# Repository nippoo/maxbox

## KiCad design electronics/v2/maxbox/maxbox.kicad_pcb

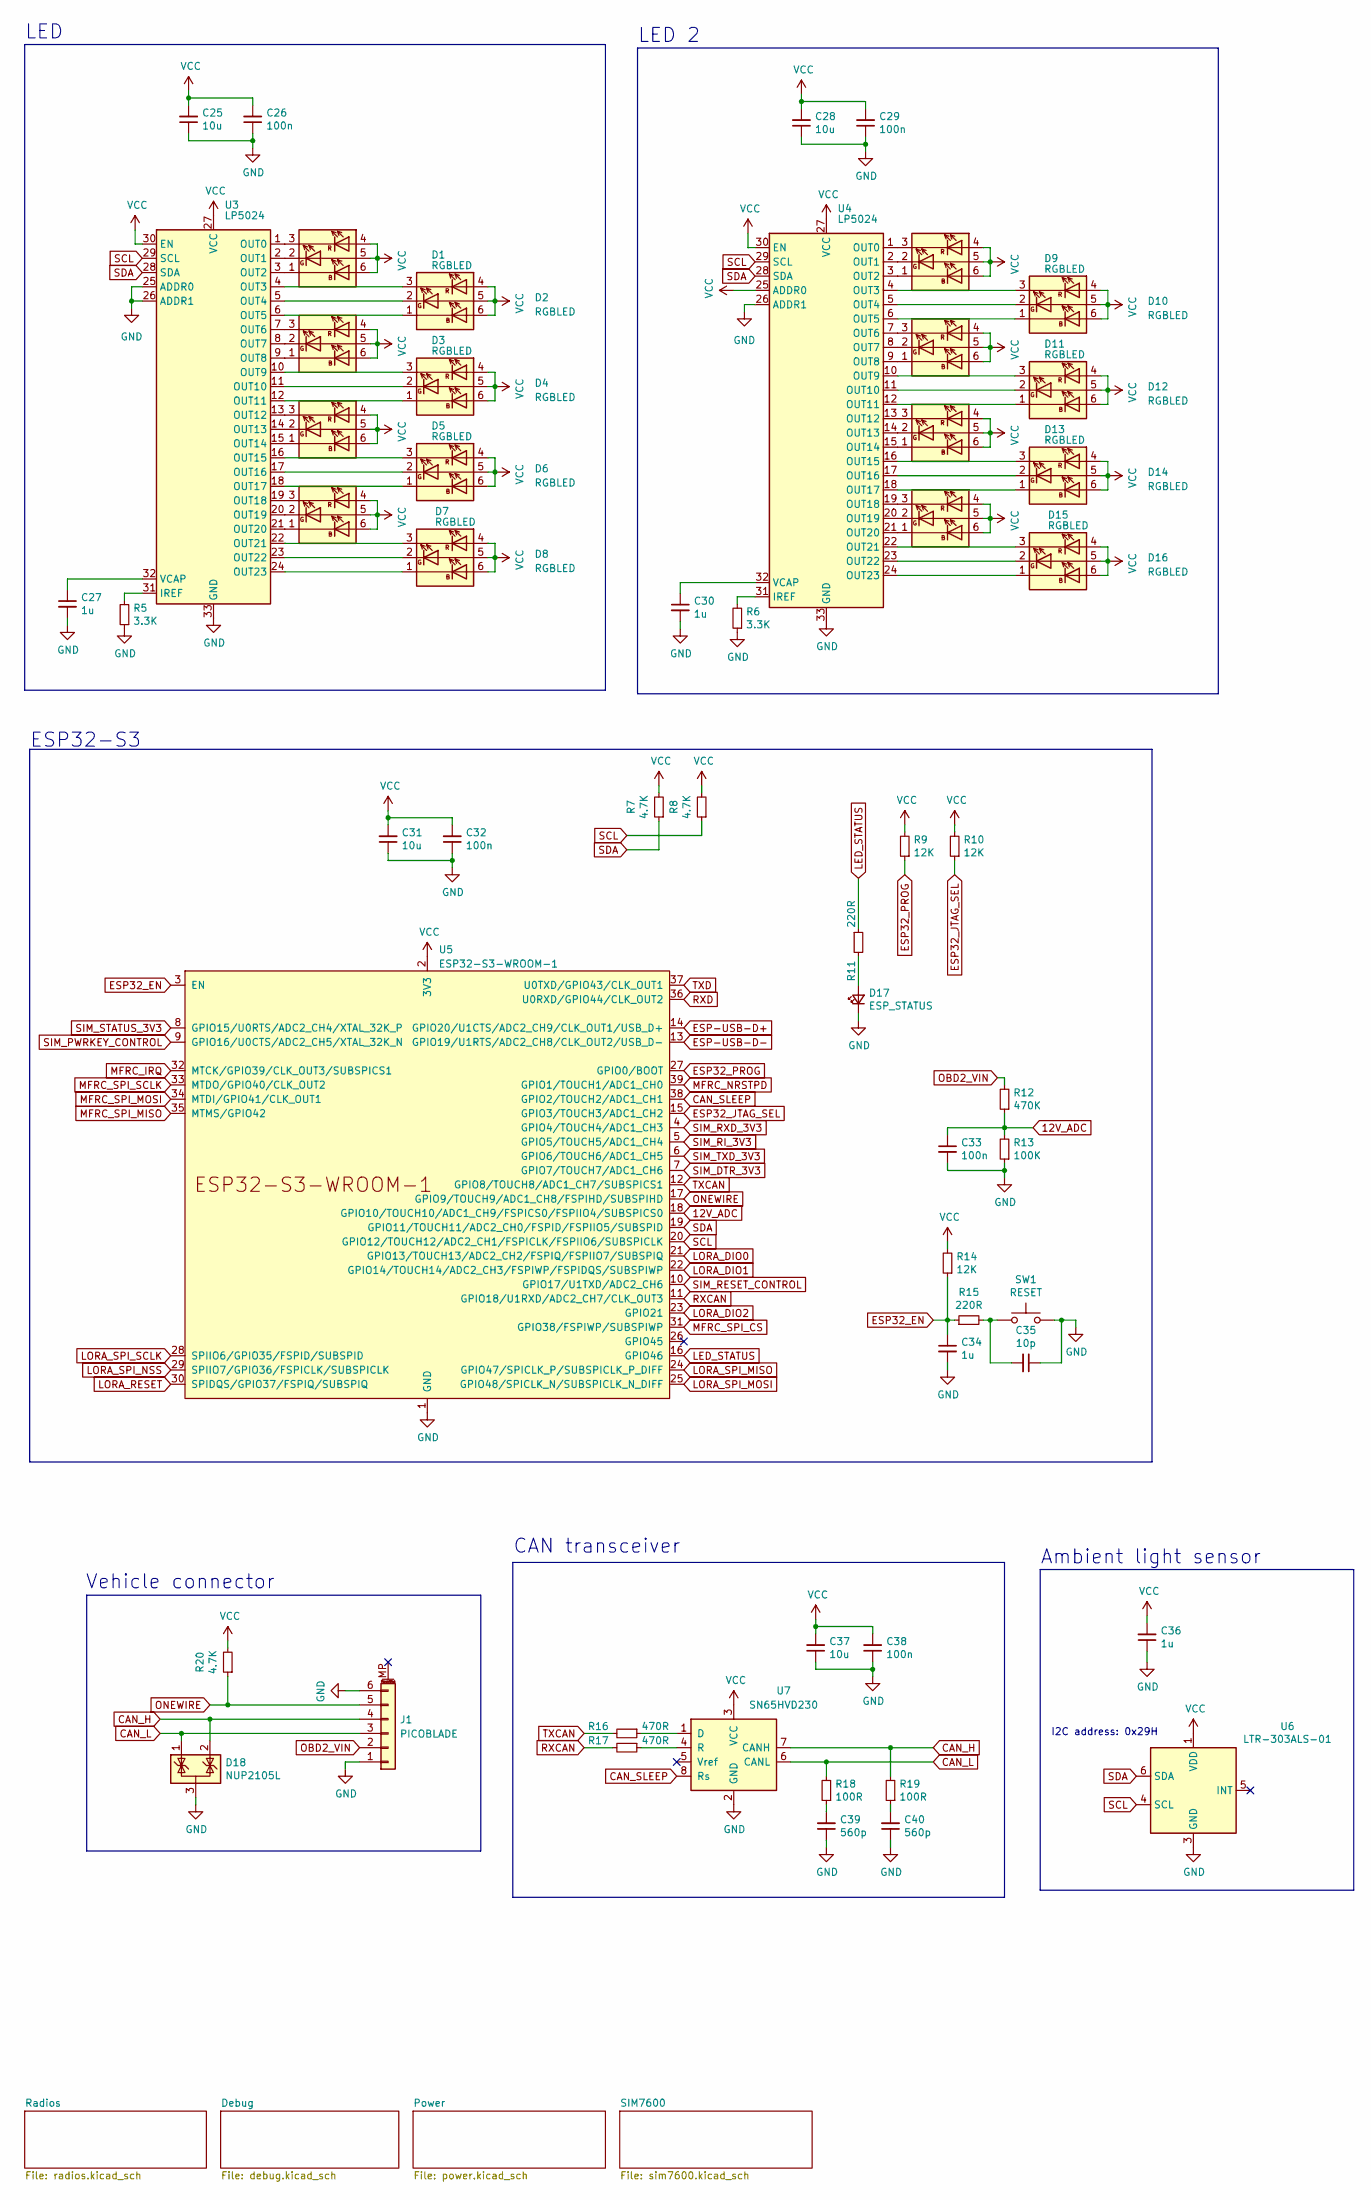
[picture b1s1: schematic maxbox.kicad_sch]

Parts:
C25, C28, C31, C37: 10u; C_0603_1608Metric; LCSC C96446
C26, C29, C32, C33, C38: 100n; C_0402_1005Metric; LCSC C307331
C27, C30, C34, C36: 1u; C_0402_1005Metric; LCSC C52923
C35: 10p; C_0402_1005Metric; LCSC C32949
C39, C40: 560p; C_0402_1005Metric; LCSC C1537
D1, D2, D3, D4, D5, D6, D7, D8, D9, D10, D11, D12, D13, D14, D15, D16: RGBLED; LED_FM-Z2727RGBA-SH; LCSC C727905
D17: ESP_STATUS; LED_0603_1608Metric; LCSC C72043
D18: NUP2105L; SOT-23; LCSC C284104
J1: PICOBLADE; Molex_PicoBlade_53261-0671_1x06-1MP_P1.25mm_Horizontal; LCSC C99277
R5, R6: 3.3K; R_0402_1005Metric; LCSC C25890
R7, R8, R20: 4.7K; R_0402_1005Metric; LCSC C105870
R9, R10, R14: 12K; R_0402_1005Metric; LCSC C25752
R11, R15: 220R; R_0402_1005Metric; LCSC C25091
R12: 470K; R_0402_1005Metric; LCSC C25790
R13: 100K; R_0402_1005Metric; LCSC C25741
R16, R17: 470R; R_0402_1005Metric; LCSC C25117
R18, R19: 100R; R_0402_1005Metric; LCSC C25076
SW1: RESET; XKB_TS-1187A-B-A-B; LCSC C318884
U3, U4: LP5024; QFN-32-1EP_4x4mm_P0.4mm_EP2.9x2.9mm_ThermalVias; LCSC C427525
U5: ESP32-S3-WROOM-1; LCSC C2913205
U6: LTR-303ALS-01; Lite-On_LTR-303ALS-01; LCSC C364577
U7: SN65HVD230; SOIC-8_3.9x4.9mm_P1.27mm; LCSC C12084

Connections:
12V_ADC: C33.1, R12.1, R13.2, U5.18 (GPIO10/TOUCH10/ADC1_CH9/FSPICS0/FSPIIO4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)
CAN_H: D18.2 (K), J1.4, R19.2, U7.7 (CANH)
CAN_L: D18.1 (K), J1.3, R18.2, U7.6 (CANL)
CAN_SLEEP: U5.38 (GPIO2/TOUCH2/ADC1_CH1), U7.8 (Rs)
ESP32_EN: C34.1, R14.1, R15.1, U5.3 (EN); also elsewhere on the board
ESP32_JTAG_SEL: R10.1, U5.15 (GPIO3/TOUCH3/ADC1_CH2)
ESP32_PROG: R9.1, U5.27 (GPIO0/BOOT); also elsewhere on the board
ESP-USB-D+: U5.14 (GPIO20/U1CTS/ADC2_CH9/CLK_OUT1/USB_D+)
ESP-USB-D-: U5.13 (GPIO19/U1RTS/ADC2_CH8/CLK_OUT2/USB_D-)
GND: C25.1, C26.1, C27.2, C28.1, C29.1, C30.2, C31.1, C32.1, C33.2, C34.2, C35.1, C36.1, C37.1, C38.1, C39.1, C40.1, D17.1 (K), D18.3 (A), J1.1, J1.6, R5.1, R6.1, R13.1, SW1.2, U3.25 (ADDR0), U3.26 (ADDR1), U3.33 (GND), U4.26 (ADDR1), U4.33 (GND), U5.1 (GND), U5.40 (GND), U5.41 (GND), U6.3 (GND), U7.2 (GND); also elsewhere on the board
LED_STATUS: R11.1, U5.16 (GPIO46)
LORA_DIO0: U5.21 (GPIO13/TOUCH13/ADC2_CH2/FSPIQ/FSPIIO7/S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); also elsewhere on the board
LORA_DIO1: U5.22 (GPIO14/TOUCH14/ADC2_CH3/FSPIWP/FSPIDQS/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); also elsewhere on the board
LORA_DIO2: U5.23 (GPIO21); also elsewhere on the board
LORA_RESET: U5.30 (SPIDQS/GPIO37/FSPIQ/SUBSPIQ); also elsewhere on the board
LORA_SPI_MISO: U5.24 (GPIO47/SPICLK_P/SUBSPICLK_P_DIFF); also elsewhere on the board
LORA_SPI_MOSI: U5.25 (GPIO48/SPICLK_N/SUBSPICLK_N_DIFF); also elsewhere on the board
LORA_SPI_NSS: U5.29 (SPIIO7/GPIO36/FSPICLK/SUBSPICLK); also elsewhere on the board
LORA_SPI_SCLK: U5.28 (SPIIO6/GPIO35/FSPID/SUBSPID); also elsewhere on the board
MFRC_IRQ: U5.32 (MTCK/GPIO39/CLK_OUT3/SUBSPICS1); also elsewhere on the board
MFRC_NRSTPD: U5.39 (GPIO1/TOUCH1/ADC1_CH0); also elsewhere on the board
MFRC_SPI_CS: U5.31 (GPIO38/FSPIWP/SUBSPIWP); also elsewhere on the board
MFRC_SPI_MISO: U5.35 (MTMS/GPIO42); also elsewhere on the board
MFRC_SPI_MOSI: U5.34 (MTDI/GPIO41/CLK_OUT1); also elsewhere on the board
MFRC_SPI_SCLK: U5.33 (MTDO/GPIO40/CLK_OUT2); also elsewhere on the board
unnamed: C35.2, R15.2, SW1.1
unnamed: C39.2, R18.1
unnamed: C40.2, R19.1
unnamed: D1.1 (KB), U3.3 (OUT2)
unnamed: D1.2 (KG), U3.2 (OUT1)
unnamed: D1.3 (KR), U3.1 (OUT0)
unnamed: D2.1 (KB), U3.6 (OUT5)
unnamed: D2.2 (KG), U3.5 (OUT4)
unnamed: D2.3 (KR), U3.4 (OUT3)
unnamed: D3.1 (KB), U3.9 (OUT8)
unnamed: D3.2 (KG), U3.8 (OUT7)
unnamed: D3.3 (KR), U3.7 (OUT6)
unnamed: D4.1 (KB), U3.12 (OUT11)
unnamed: D4.2 (KG), U3.11 (OUT10)
unnamed: D4.3 (KR), U3.10 (OUT9)
unnamed: D5.1 (KB), U3.15 (OUT14)
unnamed: D5.2 (KG), U3.14 (OUT13)
unnamed: D5.3 (KR), U3.13 (OUT12)
unnamed: D6.1 (KB), U3.18 (OUT17)
unnamed: D6.2 (KG), U3.17 (OUT16)
unnamed: D6.3 (KR), U3.16 (OUT15)
unnamed: D7.1 (KB), U3.21 (OUT20)
unnamed: D7.2 (KG), U3.20 (OUT19)
unnamed: D7.3 (KR), U3.19 (OUT18)
unnamed: D8.1 (KB), U3.24 (OUT23)
unnamed: D8.2 (KG), U3.23 (OUT22)
unnamed: D8.3 (KR), U3.22 (OUT21)
unnamed: D9.1 (KB), U4.3 (OUT2)
unnamed: D9.2 (KG), U4.2 (OUT1)
unnamed: D9.3 (KR), U4.1 (OUT0)
unnamed: D10.1 (KB), U4.6 (OUT5)
unnamed: D10.2 (KG), U4.5 (OUT4)
unnamed: D10.3 (KR), U4.4 (OUT3)
unnamed: D11.1 (KB), U4.9 (OUT8)
unnamed: D11.2 (KG), U4.8 (OUT7)
unnamed: D11.3 (KR), U4.7 (OUT6)
unnamed: D12.1 (KB), U4.12 (OUT11)
unnamed: D12.2 (KG), U4.11 (OUT10)
unnamed: D12.3 (KR), U4.10 (OUT9)
unnamed: D13.1 (KB), U4.15 (OUT14)
unnamed: D13.2 (KG), U4.14 (OUT13)
unnamed: D13.3 (KR), U4.13 (OUT12)
unnamed: D14.1 (KB), U4.18 (OUT17)
unnamed: D14.2 (KG), U4.17 (OUT16)
unnamed: D14.3 (KR), U4.16 (OUT15)
unnamed: D15.1 (KB), U4.21 (OUT20)
unnamed: D15.2 (KG), U4.20 (OUT19)
unnamed: D15.3 (KR), U4.19 (OUT18)
unnamed: D16.1 (KB), U4.24 (OUT23)
unnamed: D16.2 (KG), U4.23 (OUT22)
unnamed: D16.3 (KR), U4.22 (OUT21)
unnamed: D17.2 (A), R11.2
unnamed: R5.2, U3.31 (IREF)
unnamed: C27.1, U3.32 (VCAP)
unnamed: R6.2, U4.31 (IREF)
unnamed: C30.1, U4.32 (VCAP)
unnamed: R16.1, U7.1 (D)
unnamed: R17.1, U7.4 (R)
OBD2_VIN: J1.2, R12.2; also elsewhere on the board
ONEWIRE: J1.5, R20.1, U5.17 (GPIO9/TOUCH9/ADC1_CH8/FSPIHD/SUBSPIHD)
RXCAN: R17.2, U5.11 (GPIO18/U1RXD/ADC2_CH7/CLK_OUT3)
RXD: U5.36 (U0RXD/GPIO44/CLK_OUT2); also elsewhere on the board
SCL: R8.1, U3.29 (SCL), U4.29 (SCL), U5.20 (GPIO12/TOUCH12/ADC2_CH1/FSPICLK/FSPIIO6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), U6.4 (SCL)
SDA: R7.1, U3.28 (SDA), U4.28 (SDA), U5.19 (GPIO11/TOUCH11/ADC2_CH0/FSPID/FSPIIO5/S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), U6.6 (SDA)
SIM_DTR_3V3: U5.7 (GPIO7/TOUCH7/ADC1_CH6); also elsewhere on the board
SIM_PWRKEY_CONTROL: U5.9 (GPIO16/U0CTS/ADC2_CH5/XTAL_32K_N); also elsewhere on the board
SIM_RESET_CONTROL: U5.10 (GPIO17/U1TXD/ADC2_CH6); also elsewhere on the board
SIM_RI_3V3: U5.5 (GPIO5/TOUCH5/ADC1_CH4); also elsewhere on the board
SIM_RXD_3V3: U5.4 (GPIO4/TOUCH4/ADC1_CH3); also elsewhere on the board
SIM_STATUS_3V3: U5.8 (GPIO15/U0RTS/ADC2_CH4/XTAL_32K_P); also elsewhere on the board
SIM_TXD_3V3: U5.6 (GPIO6/TOUCH6/ADC1_CH5); also elsewhere on the board
TXCAN: R16.2, U5.12 (GPIO8/TOUCH8/ADC1_CH7/SUBSPICS1)
TXD: U5.37 (U0TXD/GPIO43/CLK_OUT1); also elsewhere on the board
VCC: C25.2, C26.2, C28.2, C29.2, C31.2, C32.2, C36.2, C37.2, C38.2, D1.4 (AR), D1.5 (AG), D1.6 (AB), D2.4 (AR), D2.5 (AG), D2.6 (AB), D3.4 (AR), D3.5 (AG), D3.6 (AB), D4.4 (AR), D4.5 (AG), D4.6 (AB), D5.4 (AR), D5.5 (AG), D5.6 (AB), D6.4 (AR), D6.5 (AG), D6.6 (AB), D7.4 (AR), D7.5 (AG), D7.6 (AB), D8.4 (AR), D8.5 (AG), D8.6 (AB), D9.4 (AR), D9.5 (AG), D9.6 (AB), D10.4 (AR), D10.5 (AG), D10.6 (AB), D11.4 (AR), D11.5 (AG), D11.6 (AB), D12.4 (AR), D12.5 (AG), D12.6 (AB), D13.4 (AR), D13.5 (AG), D13.6 (AB), D14.4 (AR), D14.5 (AG), D14.6 (AB), D15.4 (AR), D15.5 (AG), D15.6 (AB), D16.4 (AR), D16.5 (AG), D16.6 (AB), R7.2, R8.2, R9.2, R10.2, R14.2, R20.2, U3.27 (VCC), U3.30 (EN), U4.25 (ADDR0), U4.27 (VCC), U4.30 (EN), U5.2 (3V3), U6.1 (VDD), U7.3 (VCC); also elsewhere on the board

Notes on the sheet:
Ambient light sensor
CAN transceiver
LED 2
LED
I2C address: 0x29H
Vehicle connector
ESP32-S3

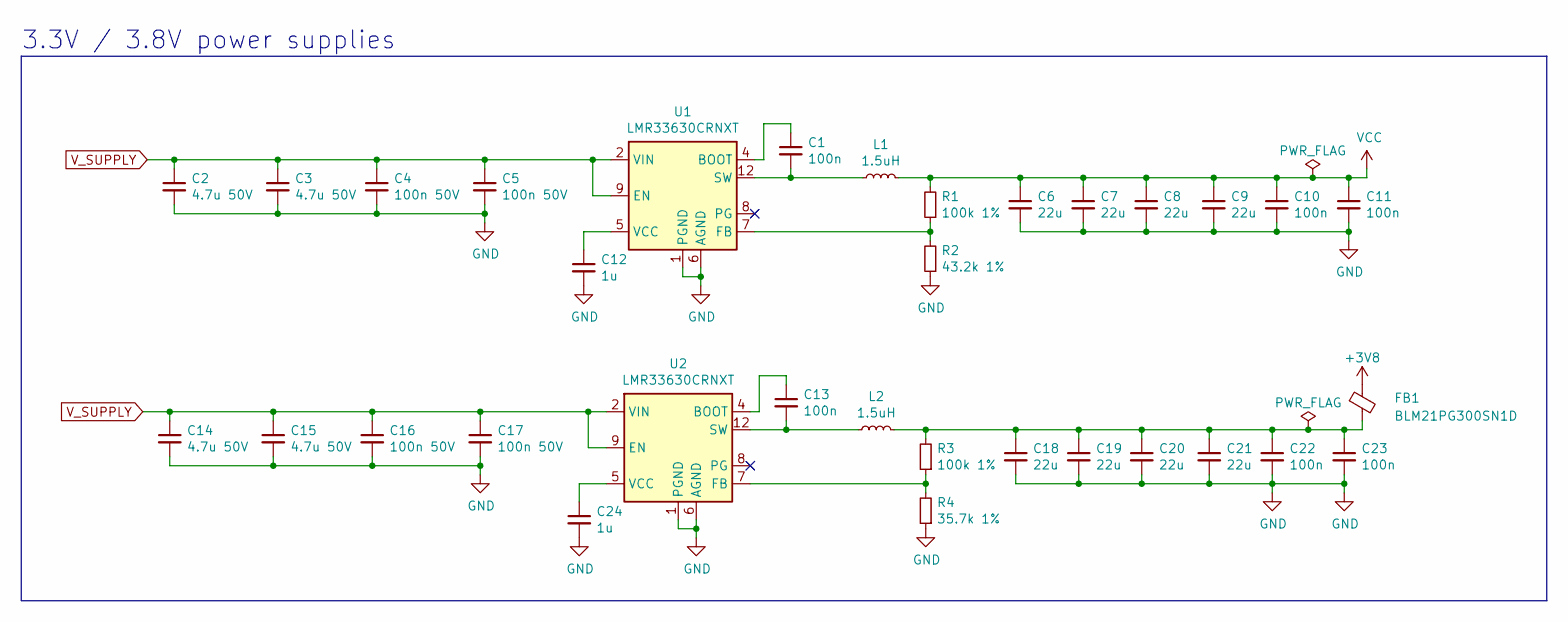
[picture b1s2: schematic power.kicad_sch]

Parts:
C1, C10, C11, C13, C22, C23: 100n; C_0402_1005Metric; LCSC C307331
C2, C3, C14, C15: 4.7u 50V; C_0603_1608Metric; LCSC C841052
C4, C5, C16, C17: 100n 50V; C_0402_1005Metric; LCSC C307331
C6, C7, C8, C9, C18, C19, C20, C21: 22u; C_0805_2012Metric; LCSC C45783
C12, C24: 1u; C_0402_1005Metric; LCSC C52923
FB1: BLM21PG300SN1D; L_0805_2012Metric; LCSC C16903
L1, L2: 1.5uH; L_Cenker_CKST252012; LCSC C3002550
R1, R3: 100k 1%; R_0402_1005Metric; LCSC C25741
R2: 43.2k 1%; R_0402_1005Metric; LCSC C409693
R4: 35.7k 1%; R_0402_1005Metric; LCSC C162861
U1, U2: LMR33630CRNXT; RNX0012B_VQFN-HR; LCSC C2071780

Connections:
+3V8: FB1.1; also elsewhere on the board
GND: C2.2, C3.2, C4.2, C5.2, C6.2, C7.2, C8.2, C9.2, C10.2, C11.2, C12.2, C14.2, C15.2, C16.2, C17.2, C18.2, C19.2, C20.2, C21.2, C22.2, C23.2, C24.2, R2.1, R4.1, U1.1 (PGND), U1.6 (AGND), U1.11 (PGND), U2.1 (PGND), U2.6 (AGND), U2.11 (PGND); also elsewhere on the board
unnamed: C18.1, C19.1, C20.1, C21.1, C22.1, C23.1, FB1.2, L2.2, R3.2
unnamed: C1.1, U1.4 (BOOT)
unnamed: R1.1, R2.2, U1.7 (FB)
unnamed: C1.2, L1.1, U1.3 (NC), U1.12 (SW)
unnamed: C12.1, U1.5 (VCC)
unnamed: C13.1, U2.4 (BOOT)
unnamed: R3.1, R4.2, U2.7 (FB)
unnamed: C13.2, L2.1, U2.3 (NC), U2.12 (SW)
unnamed: C24.1, U2.5 (VCC)
OBD2_VIN: C2.1, C3.1, C4.1, C5.1, C14.1, C15.1, C16.1, C17.1, U1.2 (VIN), U1.9 (EN), U1.10 (VIN), U2.2 (VIN), U2.9 (EN), U2.10 (VIN); also elsewhere on the board
VCC: C6.1, C7.1, C8.1, C9.1, C10.1, C11.1, L1.2, R1.2; also elsewhere on the board

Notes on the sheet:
3.3V / 3.8V power supplies

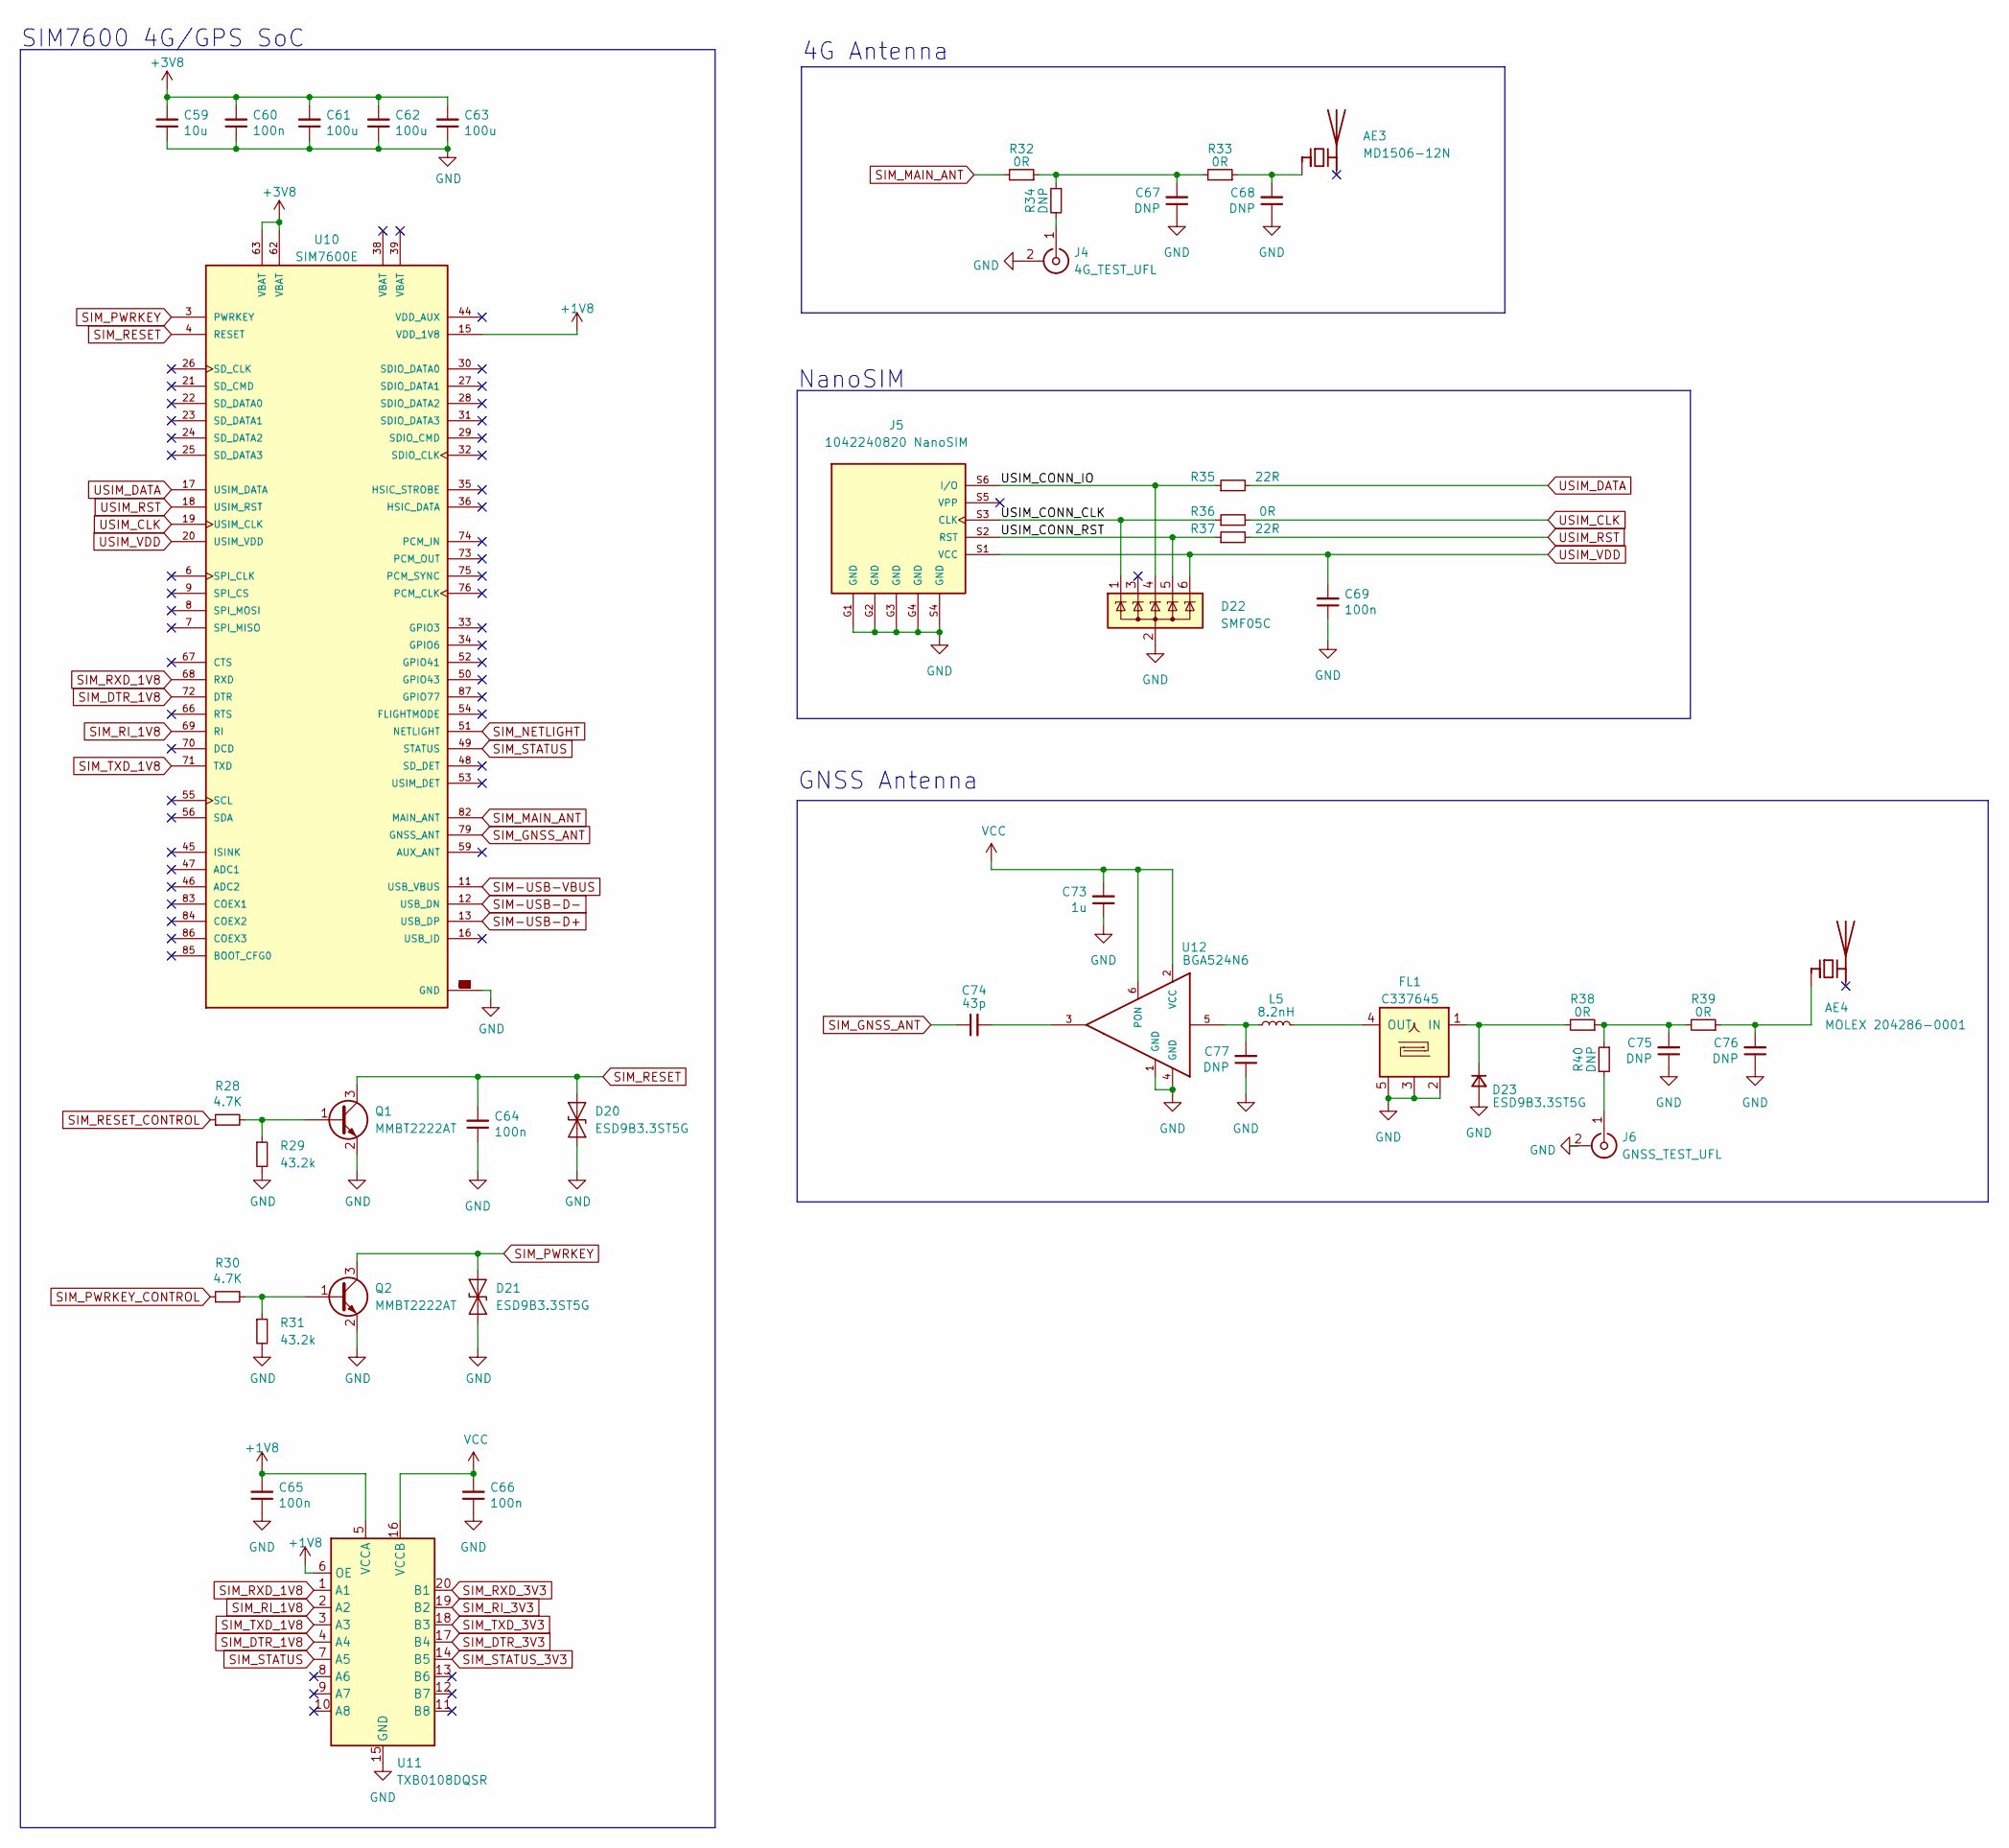
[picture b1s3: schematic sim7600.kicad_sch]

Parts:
AE3: MD1506-12N; RainSun-MD1506-12N; LCSC C239245
AE4: MOLEX 204286-0001; MOLEX 204286; LCSC C841211
C59: 10u; C_0603_1608Metric; LCSC C96446
C60, C64, C65, C66, C69: 100n; C_0402_1005Metric; LCSC C307331
C61, C62, C63: 100u; C_1206_3216Metric; LCSC C15008
C67, C68, C75, C76, C77: DNP; C_0805_2012Metric
C73: 1u; C_0402_1005Metric; LCSC C52923
C74: 43p; C_0402_1005Metric; LCSC C415393
D20, D21, D23: ESD9B3.3ST5G; D_SOD-923; LCSC C96512
D22: SMF05C; SOT-363_SC-70-6; LCSC C2995323
FL1: C337645; Filter_1411-5_1.4x1.1mm; LCSC C337645
J4: 4G_TEST_UFL; U.FL_Molex_MCRF_73412-0110_Vertical; LCSC C277719
J5: 1042240820 NanoSIM; MOLEX_104224-0820; PARTREV A; LCSC C585349
J6: GNSS_TEST_UFL; U.FL_Molex_MCRF_73412-0110_Vertical; LCSC C277719
L5: 8.2nH; L_0402_1005Metric; LCSC C307610
Q1, Q2: MMBT2222AT; SOT-523; LCSC C190608
R28, R30: 4.7K; R_0402_1005Metric; LCSC C105870
R29, R31: 43.2k; R_0402_1005Metric; LCSC C409693
R32, R33, R38, R39: 0R; R_0805_2012Metric; LCSC C304192
R34, R40: DNP; R_0805_2012Metric
R35, R37: 22R; R_0402_1005Metric; LCSC C25091
R36: 0R; R_0402_1005Metric; LCSC C17168
U10: SIM7600E; IC_SIM7600E-H; PARTREV 1.01; LCSC C2995536
U11: TXB0108DQSR; USON-20_2x4mm_P0.4mm; LCSC C427057
U12: BGA524N6; INFINEON_BGA725L6E6327FTSA1; LCSC C534158

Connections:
+1V8: C65.2, U10.15 (VDD_1V8), U11.5 (VCCA), U11.6 (OE); also elsewhere on the board
+3V8: C59.2, C60.2, C61.2, C62.2, C63.2, U10.62 (VBAT), U10.63 (VBAT); also elsewhere on the board
/SIM7600/USIM_CONN_CLK: D22.1 (K), J5.S3 (CLK), R36.1
/SIM7600/USIM_CONN_IO: D22.4 (K), J5.S6 (I/O), R35.1
/SIM7600/USIM_CONN_RST: D22.5 (K), J5.S2 (RST), R37.1
GND: C59.1, C60.1, C61.1, C62.1, C63.1, C64.1, C65.1, C66.1, C67.1, C68.1, C69.1, C73.1, C75.1, C76.1, C77.1, D20.1 (A1), D21.1 (A1), D22.2 (A), D23.2 (A), FL1.2, FL1.3, FL1.5, J4.2 (Ext), J5.G1 (GND), J5.G2 (GND), J5.G3 (GND), J5.G4 (GND), J5.S4 (GND), J6.2 (Ext), Q1.2 (E), Q2.2 (E), R29.2, R31.2, U10.1 (GND), U10.2 (GND), U10.5 (GND), U10.10 (GND), U10.14 (GND), U10.37 (GND), U10.40 (GND), U10.41 (GND), U10.43 (GND), U10.57 (GND), U10.58 (GND), U10.60 (GND), U10.61 (GND), U10.64 (GND), U10.65 (GND), U10.77 (GND), U10.78 (GND), U10.80 (GND), U10.81 (GND), U11.15 (GND), U12.1 (GND), U12.4 (GND); also elsewhere on the board
unnamed: AE3.1 (FEED), C68.2, R33.1
unnamed: AE4.1 (FEED), C76.2, R39.1
unnamed: C67.2, R32.1, R33.2, R34.1
unnamed: C74.2, U12.3
unnamed: C75.2, R38.1, R39.2, R40.1
unnamed: C77.2, L5.2, U12.5
unnamed: D23.1 (K), FL1.1 (IN), R38.2
unnamed: FL1.4 (OUT), L5.1
unnamed: J4.1 (In), R34.2
unnamed: J6.1 (In), R40.2
unnamed: Q1.1 (B), R28.2, R29.1
unnamed: Q2.1 (B), R30.2, R31.1
SIM-USB-D+: U10.13 (USB_DP)
SIM-USB-D-: U10.12 (USB_DN)
SIM-USB-VBUS: U10.11 (USB_VBUS)
SIM_DTR_1V8: U10.72 (DTR), U11.4 (A4)
SIM_DTR_3V3: U11.17 (B4); also elsewhere on the board
SIM_GNSS_ANT: C74.1, U10.79 (GNSS_ANT)
SIM_MAIN_ANT: R32.2, U10.82 (MAIN_ANT)
SIM_NETLIGHT: U10.51 (NETLIGHT)
SIM_PWRKEY: D21.2 (A2), Q2.3 (C), U10.3 (PWRKEY)
SIM_PWRKEY_CONTROL: R30.1; also elsewhere on the board
SIM_RESET: C64.2, D20.2 (A2), Q1.3 (C), U10.4 (RESET)
SIM_RESET_CONTROL: R28.1; also elsewhere on the board
SIM_RI_1V8: U10.69 (RI), U11.2 (A2)
SIM_RI_3V3: U11.19 (B2); also elsewhere on the board
SIM_RXD_1V8: U10.68 (RXD), U11.1 (A1)
SIM_RXD_3V3: U11.20 (B1); also elsewhere on the board
SIM_STATUS: U10.49 (STATUS), U11.7 (A5)
SIM_STATUS_3V3: U11.14 (B5); also elsewhere on the board
SIM_TXD_1V8: U10.71 (TXD), U11.3 (A3)
SIM_TXD_3V3: U11.18 (B3); also elsewhere on the board
USIM_CLK: R36.2, U10.19 (USIM_CLK)
USIM_DATA: R35.2, U10.17 (USIM_DATA)
USIM_RST: R37.2, U10.18 (USIM_RST)
USIM_VDD: C69.2, D22.6 (K), J5.S1 (VCC), U10.20 (USIM_VDD)
VCC: C66.2, C73.2, U11.16 (VCCB), U12.2 (VCC), U12.6 (PON); also elsewhere on the board

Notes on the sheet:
SIM7600 4G/GPS SoC
4G Antenna
GNSS Antenna
NanoSIM

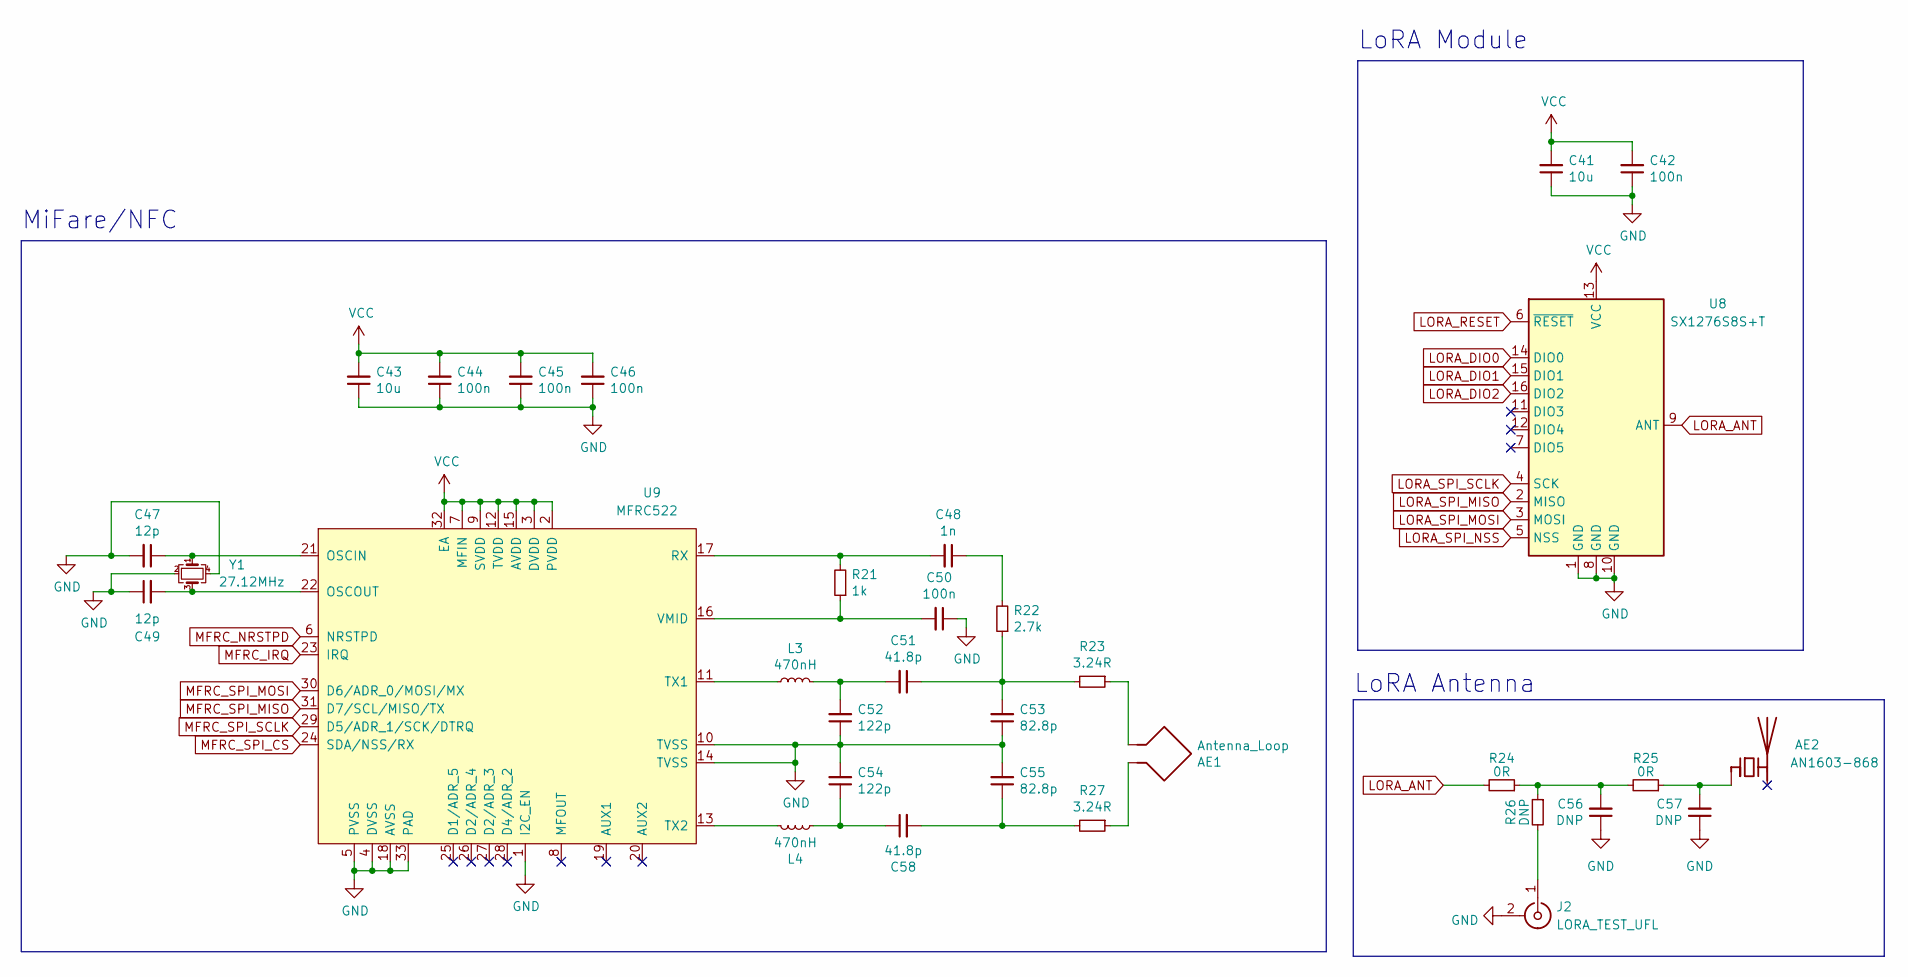
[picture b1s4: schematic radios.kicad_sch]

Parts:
AE1: Antenna_Loop; 95mm-3turn-antenna
AE2: AN1603-868; RainSun-AN1603-868; LCSC C115720
C41, C43: 10u; C_0603_1608Metric; LCSC C96446
C42, C44, C45, C46, C50: 100n; C_0402_1005Metric; LCSC C307331
C47, C49: 12p; C_0402_1005Metric; LCSC C1547
C48: 1n; C_0402_1005Metric; LCSC C1523
C51, C58: 41.8p; C_0805_2012Metric; LCSC C502147
C52, C54: 122p; C_0402_1005Metric; LCSC C161146
C53, C55: 82.8p; C_0805_2012Metric; LCSC C282712
C56, C57: DNP; C_0805_2012Metric
J2: LORA_TEST_UFL; U.FL_Molex_MCRF_73412-0110_Vertical; LCSC C277719
L3, L4: 470nH; L_0805_2012Metric; LCSC C655211
R21: 1k; R_0402_1005Metric; LCSC C11702
R22: 2.7k; R_0402_1005Metric; LCSC C323662
R23, R27: 3.24R; R_0402_1005Metric; LCSC C270612
R24, R25: 0R; R_0805_2012Metric; LCSC C304192
R26: DNP; R_0805_2012Metric
U8: SX1276S8S+T; HOPERF_RFM9XW_SMD; LCSC C718834
U9: MFRC522; VQFN-32-1EP_5x5mm_P0.5mm_EP3.5x3.5mm_ThermalVias; LCSC C11322
Y1: 27.12MHz; Crystal_SMD_3225-4Pin_3.2x2.5mm; LCSC C113669

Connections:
GND: C41.1, C42.1, C43.1, C44.1, C45.1, C46.1, C47.2, C49.1, C50.1, C52.1, C53.1, C54.2, C55.2, C56.1, C57.1, J2.2 (Ext), U8.1 (GND), U8.8 (GND), U8.10 (GND), U9.1 (I2C_EN), U9.4 (DVSS), U9.5 (PVSS), U9.10 (TVSS), U9.14 (TVSS), U9.18 (AVSS), U9.33 (PAD), Y1.2, Y1.4; also elsewhere on the board
LORA_ANT: R24.2, U8.9 (ANT)
LORA_DIO0: U8.14 (DIO0); also elsewhere on the board
LORA_DIO1: U8.15 (DIO1); also elsewhere on the board
LORA_DIO2: U8.16 (DIO2); also elsewhere on the board
LORA_RESET: U8.6 (~RESET); also elsewhere on the board
LORA_SPI_MISO: U8.2 (MISO); also elsewhere on the board
LORA_SPI_MOSI: U8.3 (MOSI); also elsewhere on the board
LORA_SPI_NSS: U8.5 (NSS); also elsewhere on the board
LORA_SPI_SCLK: U8.4 (SCK); also elsewhere on the board
MFRC_IRQ: U9.23 (IRQ); also elsewhere on the board
MFRC_NRSTPD: U9.6 (NRSTPD); also elsewhere on the board
MFRC_SPI_CS: U9.24 (SDA/NSS/RX); also elsewhere on the board
MFRC_SPI_MISO: U9.31 (D7/SCL/MISO/TX); also elsewhere on the board
MFRC_SPI_MOSI: U9.30 (D6/ADR_0/MOSI/MX); also elsewhere on the board
MFRC_SPI_SCLK: U9.29 (D5/ADR_1/SCK/DTRQ); also elsewhere on the board
unnamed: AE1.1, R27.1
unnamed: AE1.2, R23.1
unnamed: AE2.1 (FEED), C57.2, R25.1
unnamed: C48.1, R22.2
unnamed: C51.1, C53.2, R22.1, R23.2
unnamed: C51.2, C52.2, L3.2
unnamed: C54.1, C58.1, L4.1
unnamed: C55.1, C58.2, R27.2
unnamed: C56.2, R24.1, R25.2, R26.1
unnamed: J2.1 (In), R26.2
unnamed: C47.1, U9.21 (OSCIN), Y1.1
unnamed: C49.2, U9.22 (OSCOUT), Y1.3
unnamed: C48.2, R21.2, U9.17 (RX)
unnamed: L3.1, U9.11 (TX1)
unnamed: L4.2, U9.13 (TX2)
unnamed: C50.2, R21.1, U9.16 (VMID)
VCC: C41.2, C42.2, C43.2, C44.2, C45.2, C46.2, U8.13 (VCC), U9.2 (PVDD), U9.3 (DVDD), U9.7 (MFIN), U9.9 (SVDD), U9.12 (TVDD), U9.15 (AVDD), U9.32 (EA); also elsewhere on the board

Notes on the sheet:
LoRA Antenna
MiFare/NFC
LoRA Module

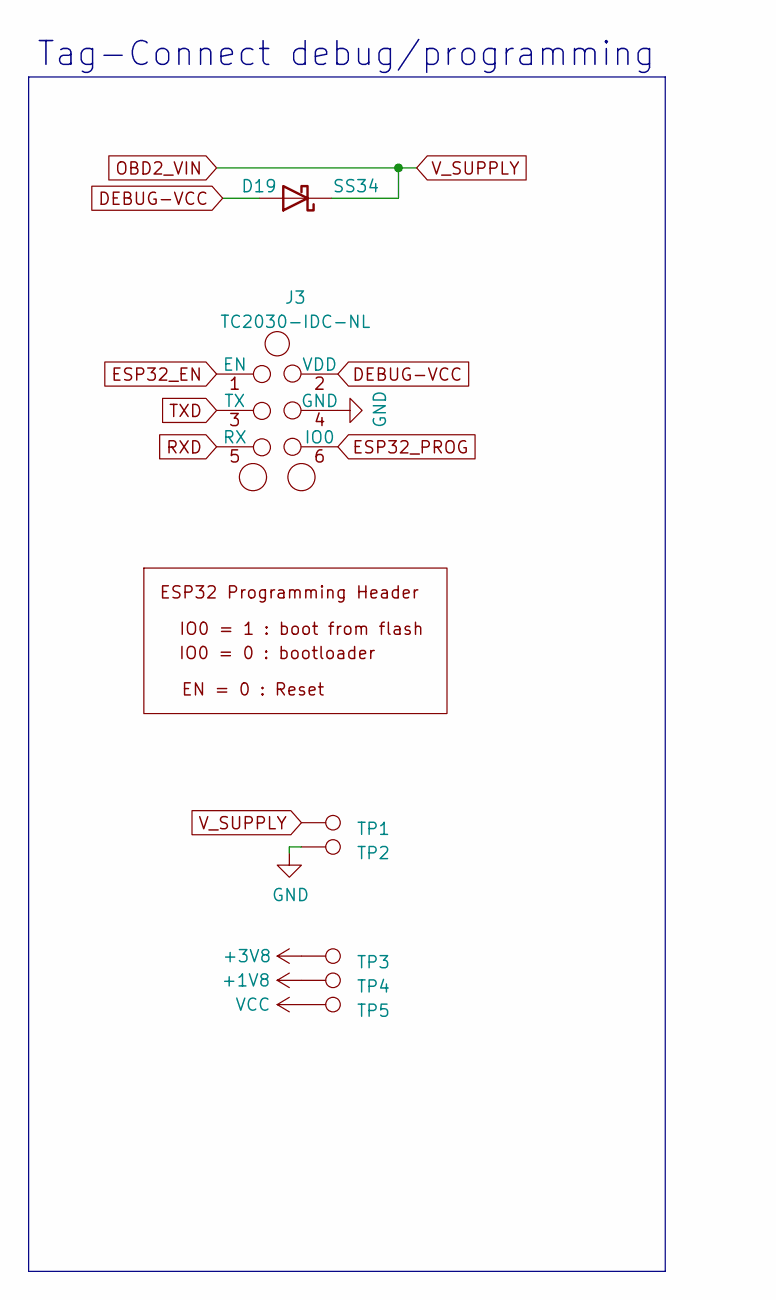
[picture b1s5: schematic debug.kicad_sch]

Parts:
D19: SS34; D_SMA; LCSC C432300
J3: TC2030-IDC-NL_ESP; Tag-Connect_TC2030-IDC-NL_2x03_P1.27mm_Vertical
TP1, TP2, TP3, TP4, TP5: TestPoint_Pad_D1.0mm

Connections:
+1V8: TP4.1; also elsewhere on the board
+3V8: TP3.1; also elsewhere on the board
DEBUG-VCC: D19.2 (A), J3.2 (VDD)
ESP32_EN: J3.1 (EN); also elsewhere on the board
ESP32_PROG: J3.6 (IO0); also elsewhere on the board
GND: J3.4 (GND), TP2.1; also elsewhere on the board
OBD2_VIN: D19.1 (K), TP1.1; also elsewhere on the board
RXD: J3.5 (RX); also elsewhere on the board
TXD: J3.3 (TX); also elsewhere on the board
VCC: TP5.1; also elsewhere on the board

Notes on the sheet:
Tag-Connect debug/programming

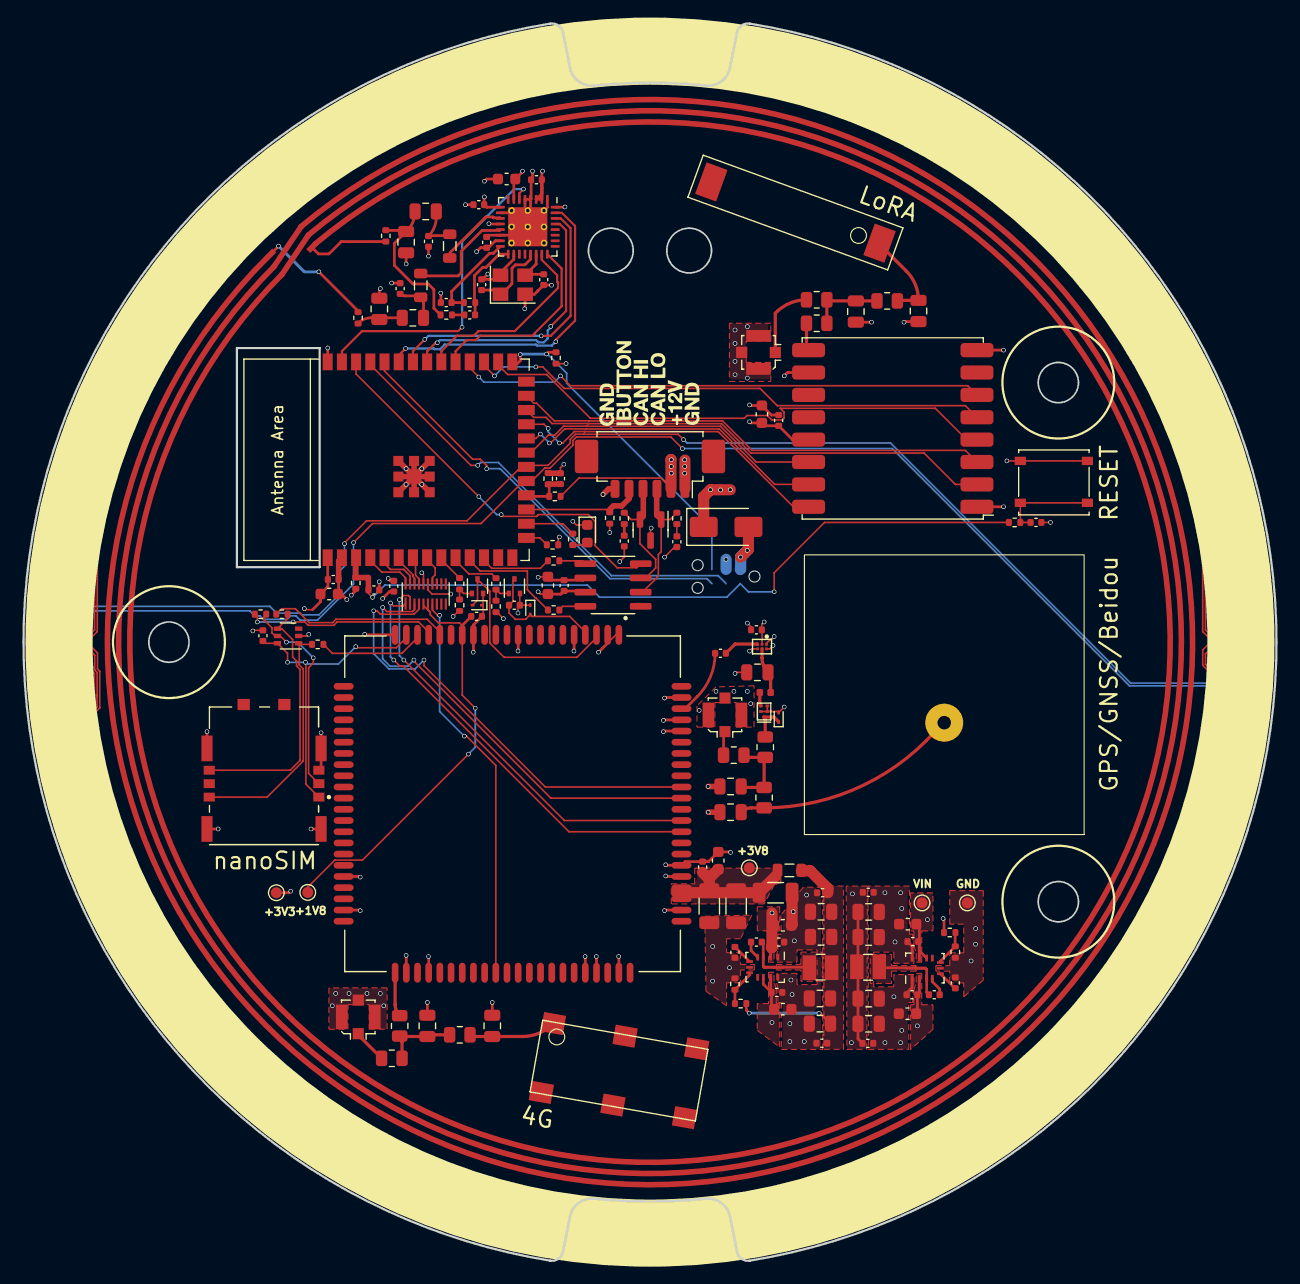
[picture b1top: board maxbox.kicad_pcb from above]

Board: 4 copper layers, 112.0 x 110.6 mm, 175 parts (1 on the bottom side), 154 nets.

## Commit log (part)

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2023-03-20 Updated firmware to compile with ESP-IDF v5
2023-03-20 Moved API parameters from hardcoded strings to menuconfig options
2023-03-20 Removed LED telemetry heartbeat flash (driving distraction risk)
2023-03-20 Moved tag handler into a non-blocking event and stopped wifi re/disconnect from blocking
2023-03-20 Don't print WiFi password to console
2023-03-21 Enable OneWire debug print mode
2023-03-21 Created v2 electronics folder
2023-05-02 v2 prototype hardware
2023-05-02 V11 firmware, minor CAN bus bugfixes
2023-05-10 Used .address_bits for SPI transmission rather than deprecated TX_BUFFER half-duplex mode for receive
2023-05-10 Updated pinout for v2 prototype
2023-05-26 Electronics: Removed debug ports
